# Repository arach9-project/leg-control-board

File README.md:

# leg-control-board

To clone repo:

```bash
git clone --recurse-submodules git@github.com:sylas-project/leg_control_board.git
```

Also this assumes you have STM32CubeCLT tools installeda [Cube CLT](https://www.st.com/en/development-tools/stm32cubeclt.html)
When installed STM32CubeIDE, run to make it work with the .elf provided:

```bash
cp \
/opt/ST/STM32CubeCLT_1.22.0/GNU-tools-for-STM32/bin/arm-none-eabi-gdb \
/Applications/STM32CubeMonitor.app/Contents/Resources/app-arm64.asar.unpacked/node_modules/@stm32/stm32cubemonitor-elfparser/bin/arm-none-eabi-gdb-macos
```

```bash
chmod +x \
/Applications/STM32CubeMonitor.app/Contents/Resources/app-arm64.asar.unpacked/node_modules/@stm32/stm32cubemonitor-elfparser/bin/arm-none-eabi-gdb-macos
```

# DRV8316 Driver

Convert functions to STM32
Make docs
Publish library and docs
Send PWM signals

# STM32 Project Template

- make template that works with neovim and clangd and cmake, setup LSP

## FOC Control

## The Complete Process Flow

```
 [User Input] Target Angle
      │
      ▼
┌─────────────────────────────────────────────────────────┐
│ 1. OUTER LOOP: Position PID                             │
│    Compare: (Target Angle - Measured Encoder Angle)     │
│    Output: Target Velocity                              │
└─────────────────────────┬───────────────────────────────┘
                          │
                          ▼
┌─────────────────────────────────────────────────────────┐
│ 2. MIDDLE LOOP: Velocity PID                            │
│    Compare: (Target Velocity - Measured Velocity)       │
│    Output: Target Torque Current (Iq_target)            │
└─────────────────────────┬───────────────────────────────┘
                          │
                          ▼
┌─────────────────────────────────────────────────────────┐
│ 3. INNER LOOP: Current (FOC) Loop                       │
│                                                         │
│    a. Read Inputs                                       │
│       • Get Angle (θ) from Encoder                      │
│       • Get Phase Currents (Ia, Ib) from ADC            │
│                                                         │
│    b. Forward Math (3-Phase AC ──► 2D DC)               │
│       • Clarke Transform: (Ia, Ib) ──► (I_alpha, I_beta)│
│       • Park Transform:   (I_alpha, I_beta, θ) ──► (Iq, Id)
│                                                         │
│    c. Torque & Magnetization PIDs                       │
│       • Iq PID: Compare (Iq_target - Iq_measured) ──► Vq│
│       • Id PID: Compare (0 - Id_measured) ──────────► Vd│
│                                                         │
│    d. Reverse Math (2D DC ──► 3-Phase Duty Cycles)     │
│       • Inverse Park:  (Vq, Vd, θ) ──► (V_alpha, V_beta)│
│       • Space Vector PWM (SVPWM):                       │
│         (V_alpha, V_beta) ──► (DutyA, DutyB, DutyC)     │
└─────────────────────────┬───────────────────────────────┘
                          │
                          ▼
┌─────────────────────────────────────────────────────────┐
│ 4. HARDWARE PWM GENERATION                              │
│    Write DutyA, DutyB, DutyC to PWM Timer Registers     │
└─────────────────────────────────────────────────────────┘
```

Stages:

| Stage | What You Build | What It Teaches / Achieves |
| --- | --- | --- |
| **Stage 1** | Open-Loop Velocity | Writes raw sine wave PWM to test power stage MOSFETs and motor wiring. No sensors needed. |
| **Stage 2** | Voltage-Mode Position Loop | Connects encoder. Runs Position PID $\rightarrow$ Inverse Park $\rightarrow$ PWM. (SimpleFOC style). |
| **Stage 3** | ADC Current Reading | Configures ADC to measure current sense resistors. Verifies phase current telemetry. |
| **Stage 4** | Full Current-Control FOC | Implements Clarke/Park & Current PIDs ($I_q, I_d$). True torque control achieved! |
| **Stage 5** | Timer + ADC DMA Interrupts | Moves Stage 4 into a hardware Timer/ADC DMA ISR for deterministic performance (ODrive style). |

Pipeline:

1. Encoder Read           ──►  Gets Rotor Angle (θ)
2. ADC Current Read       ──►  Gets Ia, Ib
3. Clarke Transform       ──►  (Ia, Ib) ──► I_alpha, I_beta
4. Park Transform         ──►  (I_alpha, I_beta, θ) ──► Iq_measured, Id_measured

5. Position PID           ──►  (Angle_target - Angle_meas) ──► Target Velocity
6. Velocity PID           ──►  (Vel_target - Vel_meas)     ──► Iq_target
7. Iq Current PID         ──►  (Iq_target - Iq_measured)   ──► Vq
8. Id Current PID         ──►  (0 - Id_measured)           ──► Vd

9. Inverse Park           ──►  (Vq, Vd, θ) ──► V_alpha, V_beta
10. Space Vector PWM      ──►  (V_alpha, V_beta) ──► DutyA, DutyB, DutyC
11. Update Timers         ──►  MOSFETs switch ──► Motor turns smoothly!

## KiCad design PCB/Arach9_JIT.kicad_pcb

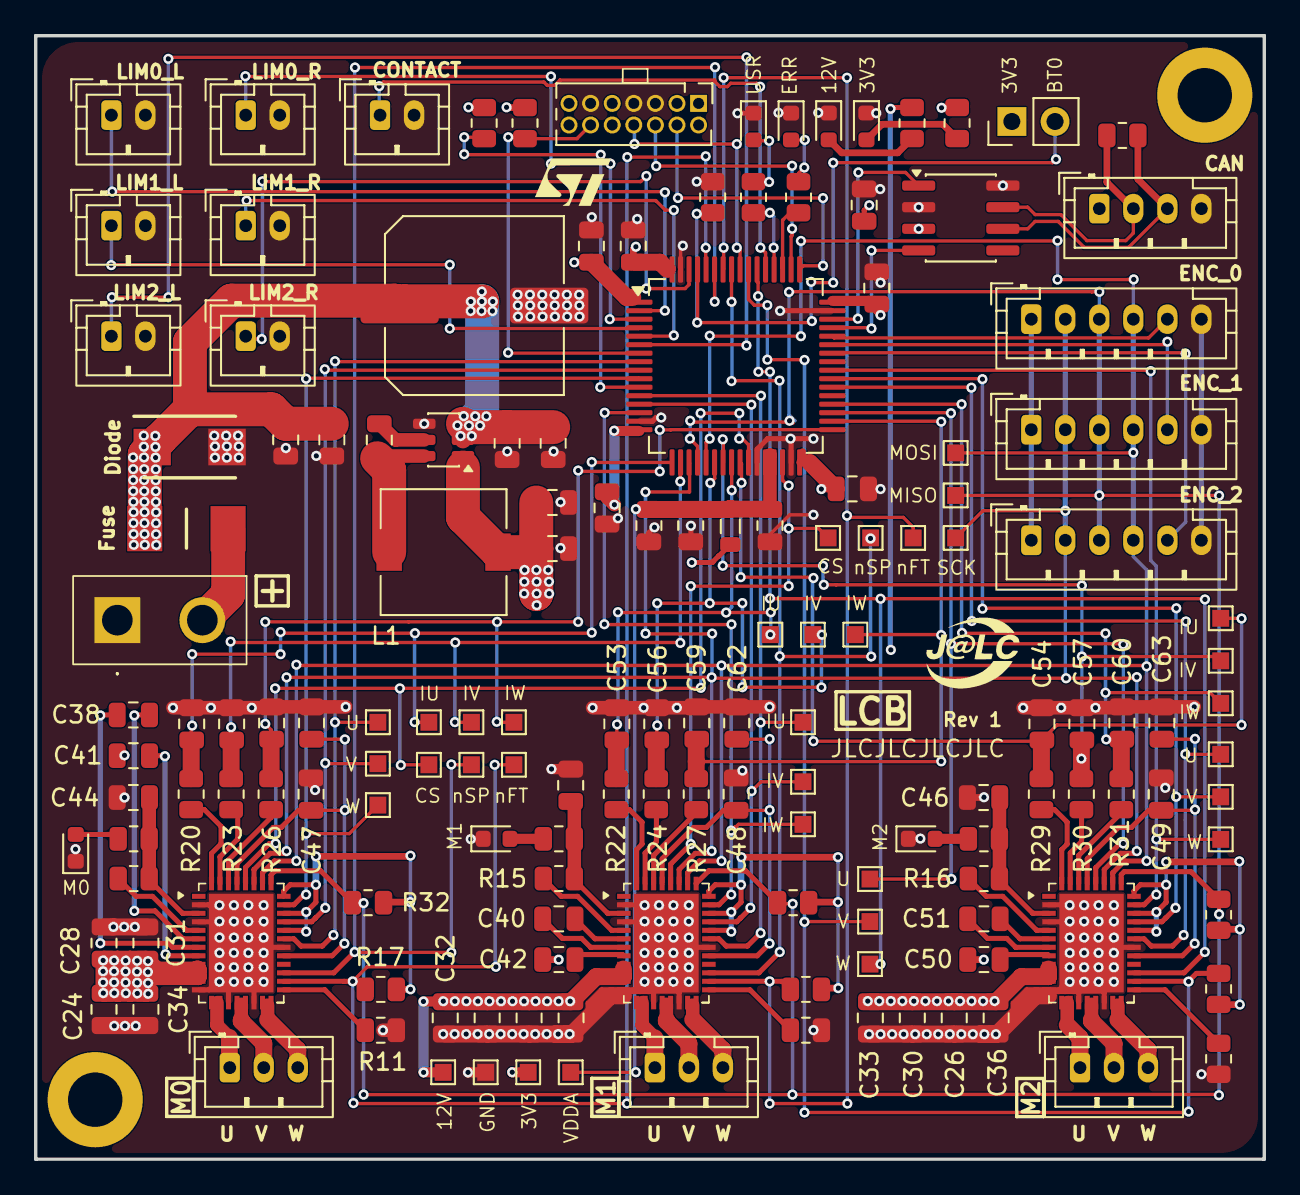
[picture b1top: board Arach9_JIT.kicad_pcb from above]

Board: 4 copper layers, 72.2 x 66.1 mm, 155 parts (0 on the bottom side), 105 nets.

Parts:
C1, C2, C3, C4, C6, C11, C14, C17, C24, C25, C26, C28, C29, C30, C31, C32, C33, C61, C62, C63: 100nF; C_0805_2012Metric
C5: 10µF; C_0805_2012Metric
C7, C16, C41, C42, C47, C48, C49, C50: 1µF; C_0805_2012Metric
C8: 10nF; C_0805_2012Metric
C9, C10: 47µF; C_0805_2012Metric
C12, C13, C44, C45, C46: 22µF; C_0805_2012Metric
C15: 470µF; C_Elec_10x10.2
C34, C35, C36: 100µF; C_0805_2012Metric
C38, C40, C51: 47nF; C_0805_2012Metric
C52, C53, C54, C55, C56, C57, C58, C59, C60: 4.7nF; C_0805_2012Metric
D1: BLUE; LED_0603_1608Metric
D2, D3, D5, D7, D8, D9: RED; LED_0603_1608Metric
D4: SMBJ15A; DIOM5436X261N
F1: Fuse_Small; FUSC6125X236N
FB1: xx; L_0805_2012Metric
H1, H2: MountingHole; MountingHole_3.2mm_M3_DIN965_Pad
IC1, IC2, IC3: DRV8316CRRGFR; QFN50P500X700X100-41N-D
J1, J2, J3, J7, J8, J9, J11: Conn_01x02; JST_PH_B2B-PH-K_1x02_P2.00mm_Vertical
J4, J13, J16: Conn_01x03; JST_PH_B3B-PH-K_1x03_P2.00mm_Vertical
J5, J10, J12: Conn_01x06; JST_PH_B6B-PH-K_1x06_P2.00mm_Vertical
J6: Conn_ST_STDC14; PinHeader_2x07_P1.27mm_Vertical
J14: Conn_01x04; JST_PH_B4B-PH-K_1x04_P2.00mm_Vertical
J17: Conn_01x02; XT30UPBF
JP1: Jumper_2_Open; PinHeader_1x02_P2.54mm_Vertical
L1: 10µF; L_7.3x7.3_H4.5
R1, R2, R3, R11, R12, R13, R32, R33, R34: 10kΩ; R_0805_2012Metric
R4, R5, R7, R8, R18, R19, R25: 150Ω; R_0805_2012Metric
R6: 120Ω; R_0805_2012Metric
R14, R15, R16: 22Ω; R_0805_2012Metric
R17, R21, R28: 5.1kΩ; R_0805_2012Metric
R20, R22, R23, R24, R26, R27, R29, R30, R31: 100Ω; R_0805_2012Metric
TP32, TP33, TP34, TP35, TP36, TP37, TP38, TP39, TP40, TP41, TP42, TP43, TP44, TP49, TP50, TP51, TP52, TP54, TP55, TP59, TP60, TP61, TP62, TP63, TP64, TP65, TP66, TP67, TP68, TP69, TP70, TP71, TP72, TP73: TestPoint; TestPoint_Pad_1.0x1.0mm
U1: STM32G431RBTx; LQFP-64_10x10mm_P0.5mm
U2: AP63203WU; TSOT-23-6
U3: SN65HVD230; SOIC-8_3.9x4.9mm_P1.27mm

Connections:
+3.3V: C1.1, C2.1, C3.1, C4.1, C5.1, C12.2, C13.2, C14.1, FB1.1, IC1.28 (INLA), IC1.30 (INLB), IC1.32 (INLC), IC2.28 (INLA), IC2.30 (INLB), IC2.32 (INLC), IC3.28 (INLA), IC3.30 (INLB), IC3.32 (INLC), J5.1, J6.3 (VCC), J10.1, J12.1, JP1.1 (A), L1.2, R1.2, R2.2, R8.2, R17.1, R21.1, R28.1, R32.1, R33.1, R34.1, TP38.1 (1_1), U1.1 (VBAT), U1.16 (VDD), U1.32 (VDD), U1.48 (VDD), U1.64 (VDD), U2.1 (FB), U3.3 (VCC)
+12V: C9.2, C10.2, C15.1, C16.1, C17.1, C24.1, C25.1, C26.1, C28.1, C29.1, C30.1, C31.1, C32.1, C33.1, C34.1, C35.1, C36.1, C41.1, C42.1, C50.1, D4.1 (K), F1.2, IC1.9 (VM_1), IC1.10 (VM_2), IC1.11 (VM_3), IC2.9 (VM_1), IC2.10 (VM_2), IC2.11 (VM_3), IC3.9 (VM_1), IC3.10 (VM_2), IC3.11 (VM_3), R7.2, TP33.1 (1_1), U2.2 (EN), U2.3 (IN)
/+3.3V_{K}: D5.2 (A), R8.1
/+12V_IN: F1.1, J17.2
/+12_{K}: D3.2 (A), R7.1
/BOOT_{0}: JP1.2 (B), R3.1, U1.61 (BOOT0)
/BST: C11.1, L1.1, U2.6 (BST)
/CAN1_RX: U1.45 (PA11), U3.4 (R)
/CAN1_TX: U1.46 (PA12), U3.1 (D)
/CAN_{1}.+: J14.2, R6.2, U3.7 (CANH)
/CAN_{1}.-: J14.3, R6.1, U3.6 (CANL)
/CONTACT: J11.1, U1.53 (PC11)
/DRV_BKIN: R1.1, U1.11 (PC3)
/ENC0_CS: J5.5, U1.44 (PA10)
/ENC1_CS: J10.5, U1.43 (PA9)
/ENC2_CS: J12.5, U1.42 (PA8)
/ERR_LED: R5.2, U1.51 (PA15)
/LIM0_L: J1.1, U1.2 (PC13)
/LIM0_R: J7.1, U1.3 (PC14)
/LIM1_L: J2.1, U1.4 (PC15)
/LIM1_R: J8.1, U1.5 (PF0)
/LIM2_L: J3.1, U1.6 (PF1)
/LIM2_R: J9.1, U1.62 (PB9)
/M0_IU_ADC: C52.1, R20.2, TP72.1 (1_1), U1.17 (PA3)
/M0_IV_ADC: C55.1, R23.2, TP73.1 (1_1), U1.18 (PA4)
/M0_IW_ADC: C58.1, R26.2, TP55.1 (1_1), U1.33 (PB11)
/M0_PWM_U: IC1.27 (INHA), TP59.1 (1_1), U1.8 (PC0)
/M0_PWM_V: IC1.29 (INHB), TP60.1 (1_1), U1.9 (PC1)
/M0_PWM_W: IC1.31 (INHC), TP61.1 (1_1), U1.10 (PC2)
/M0_nFAULT: IC1.22 (NFAULT), R17.2, TP51.1 (1_1), U1.60 (PB7)
/M0_nSCS: IC1.36 (NSCS), TP40.1 (1_1), U1.26 (PB2)
/M0_nSLEEP: IC1.23 (NSLEEP), TP39.1 (1_1), U1.59 (PB6)
/M1_IU_ADC: C53.1, R22.2, TP70.1 (1_1), U1.24 (PB0)
/M1_IV_ADC: C56.1, R24.2, TP71.1 (1_1), U1.22 (PC4)
/M1_IW_ADC: C59.1, R27.2, TP54.1 (1_1), U1.34 (PB12)
/M1_PWM_U: IC2.27 (INHA), TP62.1 (1_1), U1.12 (PA0)
/M1_PWM_V: IC2.29 (INHB), TP63.1 (1_1), U1.13 (PA1)
/M1_PWM_W: IC2.31 (INHC), TP66.1 (1_1), U1.14 (PA2)
/M1_nFAULT: IC2.22 (NFAULT), R21.2, TP50.1 (1_1), U1.58 (PB5)
/M1_nSCS: IC2.36 (NSCS), TP41.1 (1_1), U1.30 (PB10)
/M1_nSLEEP: IC2.23 (NSLEEP), TP42.1 (1_1), U1.57 (PB4)
/M2_IU_ADC: C54.1, R29.2, TP69.1 (1_1), U1.25 (PB1)
/M2_IV_ADC: C57.1, R30.2, TP68.1 (1_1), U1.23 (PC5)
/M2_IW_ADC: C60.1, R31.2, TP52.1 (1_1), U1.36 (PB14)
/M2_PWM_U: IC3.27 (INHA), TP64.1 (1_1), U1.38 (PC6)
/M2_PWM_V: IC3.29 (INHB), TP65.1 (1_1), U1.39 (PC7)
/M2_PWM_W: IC3.31 (INHC), TP67.1 (1_1), U1.40 (PC8)
/M2_nFAULT: IC3.22 (NFAULT), R28.2, TP49.1 (1_1), U1.55 (PD2)
/M2_nSCS: IC3.36 (NSCS), TP43.1 (1_1), U1.35 (PB13)
/M2_nSLEEP: IC3.23 (NSLEEP), TP44.1 (1_1), U1.54 (PC12)
/Motor_Driver_1/+3.3V_{K}: D7.2 (A), R18.1
/Motor_Driver_1/OUTA: IC1.13 (OUTA_1), IC1.14 (OUTA_2), J4.1
/Motor_Driver_1/OUTB: IC1.16 (OUTB_1), IC1.17 (OUTB_2), J4.2
/Motor_Driver_1/OUTC: IC1.19 (OUTC_1), IC1.20 (OUTC_2), J4.3
/Motor_Driver_2/+3.3V_{K}: D8.2 (A), R19.1
/Motor_Driver_2/OUTA: IC2.13 (OUTA_1), IC2.14 (OUTA_2), J13.1
/Motor_Driver_2/OUTB: IC2.16 (OUTB_1), IC2.17 (OUTB_2), J13.2
/Motor_Driver_2/OUTC: IC2.19 (OUTC_1), IC2.20 (OUTC_2), J13.3
/Motor_Driver_3/+3.3V_{K}: D9.2 (A), R25.1
/Motor_Driver_3/OUTA: IC3.13 (OUTA_1), IC3.14 (OUTA_2), J16.1
/Motor_Driver_3/OUTB: IC3.16 (OUTB_1), IC3.17 (OUTB_2), J16.2
/Motor_Driver_3/OUTC: IC3.19 (OUTC_1), IC3.20 (OUTC_2), J16.3
/NRST: J6.12 (~RST), R2.1, U1.7 (NRST)
/SPI1_MISO: IC1.33 (SDO), IC2.33 (SDO), IC3.33 (SDO), J5.3, J10.3, J12.3, R32.2, R33.2, R34.2, TP37.1 (1_1), U1.20 (PA6)
/SPI1_MOSI: IC1.34 (SDI), IC2.34 (SDI), IC3.34 (SDI), J5.4, J10.4, J12.4, TP36.1 (1_1), U1.21 (PA7)
/SPI1_SCK: IC1.35 (SCLK), IC2.35 (SCLK), IC3.35 (SCLK), J5.2, J10.2, J12.2, TP35.1 (1_1), U1.19 (PA5)
/SW: C11.2, U2.5 (SW)
/SWCLK: J6.6 (JCLK/SWCLK), U1.50 (PA14)
/SWDIO: J6.4 (JTMS/SWDIO), U1.49 (PA13)
/SWO: J6.8 (JTDO/SWO), U1.56 (PB3)
/USR_LED: R4.2, U1.52 (PC10)
GND: C1.2, C2.2, C3.2, C4.2, C5.2, C6.2, C7.2, C8.2, C9.1, C10.1, C12.1, C13.1, C14.2, C15.2, C16.2, C17.2, C24.2, C25.2, C26.2, C28.2, C29.2, C30.2, C31.2, C32.2, C33.2, C34.2, C35.2, C36.2, C44.2, C45.2, C46.2, C47.2, C48.2, C49.2, C52.2, C53.2, C54.2, C55.2, C56.2, C57.2, C58.2, C59.2, C60.2, C61.2, C62.2, C63.2, D1.1 (K), D2.1 (K), D3.1 (K), D4.2 (A), D5.1 (K), D7.1 (K), D8.1 (K), D9.1 (K), IC1.2 (AGND_1), IC1.4 (GND_BK), IC1.12 (PGND_1), IC1.15 (PGND_2), IC1.18 (PGND_3), IC1.26 (AGND_2), IC1.41 (EP), IC2.2 (AGND_1), IC2.4 (GND_BK), IC2.12 (PGND_1), IC2.15 (PGND_2), IC2.18 (PGND_3), IC2.26 (AGND_2), IC2.41 (EP), IC3.2 (AGND_1), IC3.4 (GND_BK), IC3.12 (PGND_1), IC3.15 (PGND_2), IC3.18 (PGND_3), IC3.26 (AGND_2), IC3.41 (EP), J1.2, J2.2, J3.2, J5.6, J6.5 (GND), J6.7 (GND), J6.11 (GNDDetect), J7.2, J8.2, J9.2, J10.6, J11.2, J12.6, J14.4, J17.1, R3.2, R11.2, R12.2, R13.2, TP32.1 (1_1), U1.15 (VSS), U1.27 (VSSA), U1.31 (VSS), U1.47 (VSS), U1.63 (VSS), U2.4 (GND), U3.2 (GND), U3.8 (Rs)
unnamed: D1.2 (A), R4.1
unnamed: D2.2 (A), R5.1
unnamed: C47.1, C61.1, IC1.25 (AVDD), IC1.37 (VREF/_ILIM)
unnamed: C41.2, IC1.8 (CP)
unnamed: C38.1, IC1.7 (CPH)
unnamed: C38.2, IC1.6 (CPL)
unnamed: IC1.21 (DRVOFF), R11.1
unnamed: C44.1, IC1.3 (FB_BK), R14.2, R18.2
unnamed: IC1.40 (SOA), R20.1
unnamed: IC1.39 (SOB), R23.1
unnamed: IC1.38 (SOC), R26.1
unnamed: IC1.5 (SW_BK), R14.1
unnamed: C48.1, C62.1, IC2.25 (AVDD), IC2.37 (VREF/_ILIM)
unnamed: C42.2, IC2.8 (CP)
unnamed: C40.1, IC2.7 (CPH)
unnamed: C40.2, IC2.6 (CPL)
unnamed: IC2.21 (DRVOFF), R12.1
unnamed: C45.1, IC2.3 (FB_BK), R15.2, R19.2
unnamed: IC2.40 (SOA), R22.1
unnamed: IC2.39 (SOB), R24.1
unnamed: IC2.38 (SOC), R27.1
unnamed: IC2.5 (SW_BK), R15.1
unnamed: C49.1, C63.1, IC3.25 (AVDD), IC3.37 (VREF/_ILIM)
unnamed: C50.2, IC3.8 (CP)
unnamed: C51.1, IC3.7 (CPH)
unnamed: C51.2, IC3.6 (CPL)
unnamed: IC3.21 (DRVOFF), R13.1
unnamed: C46.1, IC3.3 (FB_BK), R16.2, R25.2
unnamed: IC3.40 (SOA), R29.1
unnamed: IC3.39 (SOB), R30.1
unnamed: IC3.38 (SOC), R31.1
unnamed: IC3.5 (SW_BK), R16.1
VDDA: C6.1, C7.1, C8.1, FB1.2, TP34.1 (1_1), U1.28 (VREF+), U1.29 (VDDA)

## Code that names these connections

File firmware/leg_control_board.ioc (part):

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Mcu.Name=STM32G431R(6-8-B)Tx
Mcu.Package=LQFP64
Mcu.UserName=STM32G431RBTx
PA0.GPIOParameters=GPIO_Label
PA0.GPIO_Label=M1_PWM_U
PA0.Signal=S_TIM2_CH1
PA1.GPIOParameters=GPIO_Label
PA1.GPIO_Label=M1_PWM_V
PA1.Signal=S_TIM2_CH2
PA10.GPIOParameters=GPIO_Label
PA10.GPIO_Label=ENC0_CS
PA10.Signal=GPIO_Output
PA11.GPIOParameters=GPIO_Label
PA11.GPIO_Label=CAN1_RX
PA11.Mode=FDCAN_Activate
PA11.Signal=FDCAN1_RX
PA12.GPIOParameters=GPIO_Label
PA12.GPIO_Label=CAN1_TX
PA12.Mode=FDCAN_Activate
PA12.Signal=FDCAN1_TX
PA13.GPIOParameters=GPIO_Label
PA13.GPIO_Label=SWDIO
PA13.Mode=Trace_Asynchronous_SW
PA13.Signal=SYS_JTMS-SWDIO
PA14.GPIOParameters=GPIO_Label
PA14.GPIO_Label=SWCLK
PA14.Mode=Trace_Asynchronous_SW
PA14.Signal=SYS_JTCK-SWCLK
PA15.GPIOParameters=GPIO_Label
PA15.GPIO_Label=ERR_LED
PA15.Signal=GPIO_Output
PA2.GPIOParameters=GPIO_Label
PA2.GPIO_Label=M1_PWM_W
PA2.Signal=S_TIM2_CH3
PA3.GPIOParameters=GPIO_Label
PA3.GPIO_Label=M0_IU_ADC
PA3.Mode=IN4-Single-Ended
PA3.Signal=ADC1_IN4
PA4.GPIOParameters=GPIO_Label
PA4.GPIO_Label=M0_IV_ADC
PA4.Mode=IN17-Single-Ended
PA4.Signal=ADC2_IN17
PA5.Mode=Full_Duplex_Master
PA5.Signal=SPI1_SCK
PA6.Mode=Full_Duplex_Master
PA6.Signal=SPI1_MISO
PA7.Mode=Full_Duplex_Master
PA7.Signal=SPI1_MOSI
PA8.GPIOParameters=GPIO_Label
PA8.GPIO_Label=ENC2_CS
PA8.Signal=GPIO_Output
PA9.GPIOParameters=GPIO_Label
PA9.GPIO_Label=ENC1_CS
PA9.Signal=GPIO_Output
PB0.GPIOParameters=GPIO_Label
PB0.GPIO_Label=M1_IU_ADC
PB0.Mode=IN15-Single-Ended
PB0.Signal=ADC1_IN15
PB1.GPIOParameters=GPIO_Label
PB1.GPIO_Label=M2_IU_ADC
PB1.Mode=IN12-Single-Ended
PB1.Signal=ADC1_IN12
PB10.GPIOParameters=GPIO_Label
PB10.GPIO_Label=M1_nSCS
PB10.Signal=GPIO_Output
PB11.GPIOParameters=GPIO_Label
PB11.GPIO_Label=M0_IW_ADC
PB11.Mode=IN14-Single-Ended
PB11.Signal=ADC1_IN14
PB12.GPIOParameters=GPIO_Label
PB12.GPIO_Label=M1_IW_ADC
PB12.Mode=IN11-Single-Ended
PB12.Signal=ADC1_IN11
PB13.GPIOParameters=GPIO_Label
PB13.GPIO_Label=M2_nSCS
PB13.Signal=GPIO_Output
PB14.GPIOParameters=GPIO_Label
PB14.GPIO_Label=M2_IW_ADC
PB14.Mode=IN5-Single-Ended
PB14.Signal=ADC1_IN5
PB2.GPIOParameters=GPIO_Label
PB2.GPIO_Label=M0_nSCS
PB2.Signal=GPIO_Output
PB3.GPIOParameters=GPIO_Label
PB3.GPIO_Label=SWO
PB3.Mode=Trace_Asynchronous_SW
PB3.Signal=SYS_JTDO-SWO
PB4.GPIOParameters=GPIO_Label
PB4.GPIO_Label=M1_nSLEEP
PB4.Signal=GPXTI4
PB5.GPIOParameters=GPIO_Label
PB5.GPIO_Label=M1_nFAULT
PB5.Signal=GPXTI5
PB6.GPIOParameters=GPIO_Label
PB6.GPIO_Label=M0_nSLEEP
PB6.Signal=GPIO_Output
PB7.GPIOParameters=GPIO_Label
PB7.GPIO_Label=M0_nFAULT
PB7.Signal=GPXTI7
PB9.GPIOParameters=GPIO_Label
PB9.GPIO_Label=LIM2_R
PB9.Signal=GPXTI9
PC0.GPIOParameters=GPIO_Label
PC0.GPIO_Label=M0_PWM_U
PC0.Signal=S_TIM1_CH1
PC1.GPIOParameters=GPIO_Label
PC1.GPIO_Label=M0_PWM_V
PC1.Signal=S_TIM1_CH2
PC10.GPIOParameters=GPIO_Label
PC10.GPIO_Label=USR_LED
PC10.Signal=GPIO_Output
PC11.GPIOParameters=GPIO_Label
PC11.GPIO_Label=CONTACT
PC11.Signal=GPXTI11
PC12.GPIOParameters=GPIO_Label
PC12.GPIO_Label=M2_nSLEEP
PC12.Signal=GPXTI12
PC13.GPIOParameters=GPIO_Label
PC13.GPIO_Label=LIM0_L
PC13.Signal=GPXTI13
PC14-OSC32_IN.GPIOParameters=GPIO_Label
PC14-OSC32_IN.GPIO_Label=LIM0_R
PC14-OSC32_IN.Signal=GPXTI14
PC15-OSC32_OUT.GPIOParameters=GPIO_Label
PC15-OSC32_OUT.GPIO_Label=LIM1_L
PC15-OSC32_OUT.Signal=GPXTI15
PC2.GPIOParameters=GPIO_Label
PC2.GPIO_Label=M0_PWM_W
PC2.Signal=S_TIM1_CH3
PC3.GPIOParameters=GPIO_Label
PC3.GPIO_Label=DRV_BKIN
PC3.Signal=TIM1_BKIN2
PC4.GPIOParameters=GPIO_Label
PC4.GPIO_Label=M1_IV_ADC
PC4.Mode=IN5-Single-Ended
PC4.Signal=ADC2_IN5
PC5.GPIOParameters=GPIO_Label
PC5.GPIO_Label=M2_IV_ADC
PC5.Mode=IN11-Single-Ended
PC5.Signal=ADC2_IN11
PC6.GPIOParameters=GPIO_Label
PC6.GPIO_Label=M2_PWM_U
PC6.Signal=S_TIM8_CH1
PC7.GPIOParameters=GPIO_Label
PC7.GPIO_Label=M2_PWM_V
PC7.Signal=S_TIM8_CH2
PC8.GPIOParameters=GPIO_Label
PC8.GPIO_Label=M2_PWM_W
PC8.Signal=S_TIM8_CH3
PD2.GPIOParameters=GPIO_Label
PD2.GPIO_Label=M2_nFAULT
PD2.Signal=GPXTI2
PF0-OSC_IN.GPIOParameters=GPIO_Label
PF0-OSC_IN.GPIO_Label=LIM1_R
PF0-OSC_IN.Signal=GPXTI0
PF1-OSC_OUT.GPIOParameters=GPIO_Label
PF1-OSC_OUT.GPIO_Label=LIM2_L
PF1-OSC_OUT.Signal=GPXTI1
RCC.HSE_VALUE=8000000
RCC.SYSCLKFreq_VALUE=16000000
board=custom
